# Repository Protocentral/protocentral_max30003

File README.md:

# ProtoCentral MAX30003 — Single‑lead ECG Breakout

Arduino library and examples for the MAX30003 single‑lead ECG analog front end.

## Highlights
- MAX30003 AFE: single‑lead ECG, ultra‑low power operation, integrated R‑R (RTOR) detection and QRS timing.
- Board: ProtoCentral breakout with level selection for 3.3V/5V systems, SPI interface, and INT pin for event/RTOR notifications.

## Quick features
- Single‑lead ECG measurement (24‑bit ADC samples)
- On‑chip R‑R (RTOR) detection and heart‑rate calculation
- Low power: suitable for battery powered wearables
- SPI interface; interrupt output for beat/flags

Wiring (Arduino defaults used in examples)

| MAX30003 signal | Arduino pin | Notes |
|-----------------|-------------|-------|
| MISO            | D12         | SPI MISO |
| MOSI            | D11         | SPI MOSI |
| SCLK            | D13         | SPI SCK  |
| CS              | D4          | Chip select (examples default) |
| INT1            | D2          | Interrupt / RTOR flag |
| VCC / 3V3       | 3.3V / 5V   | Power (match board jumper) |
| GND             | GND         | Ground |

## Quick start (example)

```cpp
#include <SPI.h>
#include "protocentral_max30003.h"

// Use chip select pin D4 (examples default)
MAX30003 max30003(4);

void setup() {
  Serial.begin(115200);
  SPI.begin();

  if (!max30003.readDeviceID()) {
    while (1) { delay(1000); }
  }

  max30003.begin();         // start sensor, default sampling
  max30003.setSamplingRate(MAX30003::SRATE_1000HZ); // optional: change sample rate
}

void loop() {
  int32_t ecg = 0;
  if (max30003.readEcgSample(ecg)) {   // returns true when a new sample is available
    Serial.println(ecg);               // 24‑bit sign‑extended ADC value
  }

  // RTOR / heart rate (library keeps latest values)
  max30003.updateHeartRate();
  Serial.print("HR:"); Serial.print(max30003.heartRate());
  Serial.print(" RR(ms):"); Serial.println(max30003.rrInterval());

  delay(8);
}
```

## Examples
- `examples/01-ecg-openview` — OpenView / UART packet streaming example
- `examples/02-ecg-plotter` — Arduino Serial Plotter output
- `examples/03-hr-rtor` — Heart‑rate and RTOR demonstration

## Build & upload using arduino-cli

```bash
arduino-cli compile --fqbn arduino:renesas_uno:minima --libraries /path/to/Arduino/libraries /path/to/protocentral_max30003/examples/02-ecg-plotter
arduino-cli upload -p /dev/ttyACM0 -b arduino:renesas_uno:minima -i /tmp/build/02-ecg-plotter.ino.bin
```

## Documentation & support
- Board and getting started: https://docs.protocentral.com/getting-started-with-max30003/
- Product page: https://www.protocentral.com/open-medical-devices/1149-protocentral-max30003-single-lead-ecg-breakout-board.html

## Licenses
- Hardware: CERN-OHL-P v2 (see `LICENSE.md`)
- Software: MIT (see `LICENSE.md`)

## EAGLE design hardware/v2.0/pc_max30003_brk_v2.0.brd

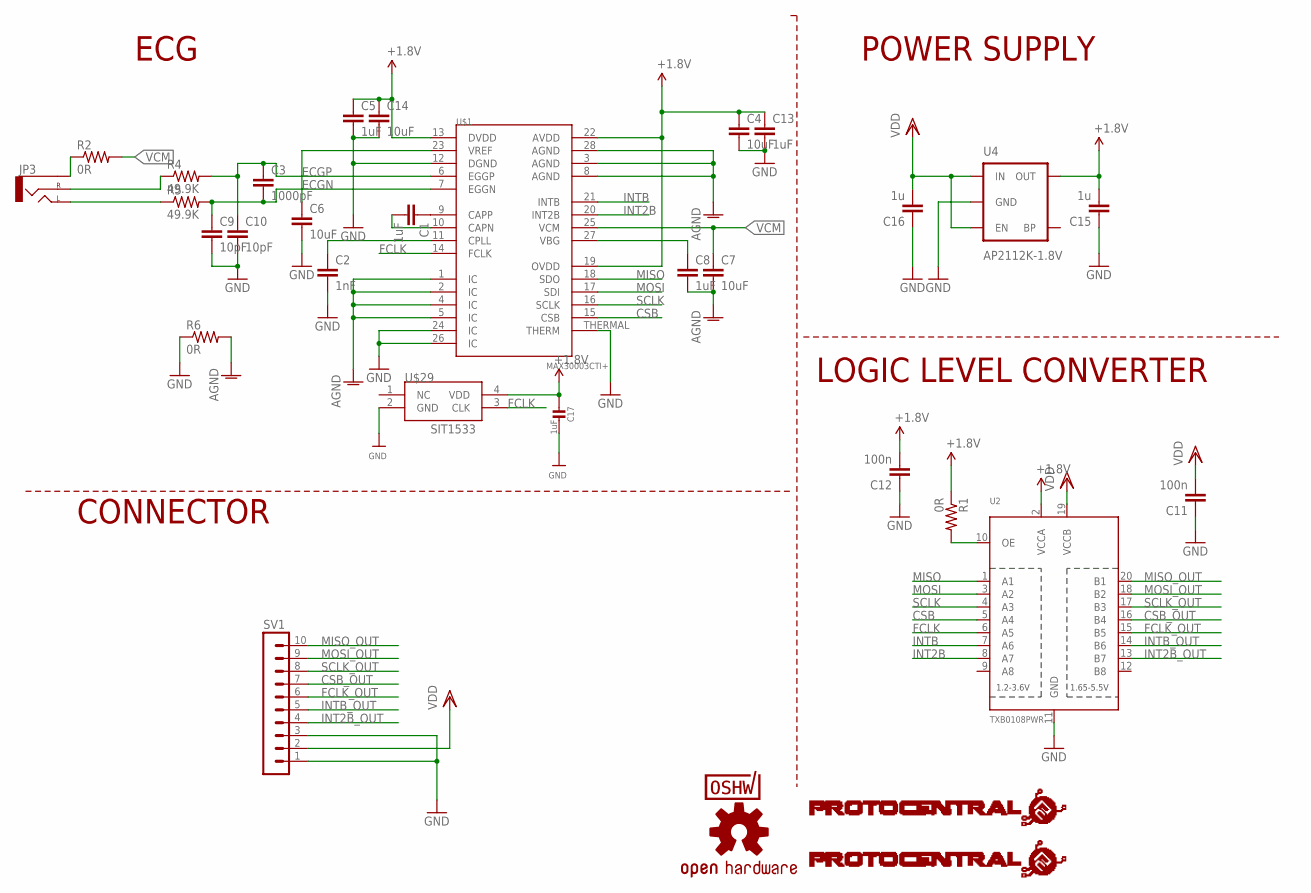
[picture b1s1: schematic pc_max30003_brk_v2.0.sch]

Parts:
C1, C5, C8, C13: 1uF; C0805
C2: 1nF; C0805
C3: 1000pF; C0402
C4, C6, C7, C14: 10uF; C0805
C9, C10: 10pF; C0402
C11, C12: 100n; C0402
C15, C16: 1u; C0805
C17: 1uF; _0402
JP3: AUDIO-JACKSMD2; AUDIO-JACK-3.5MM-SMD
R1, R2, R6: 0R; 0805
R4, R5: 49.9K; 0805
SV1: MA10-1
U2: TXB0108PWR; TSSOP20
U4: AP2112K-1.8V; SOT23-5
U$1: MAX30003CTI+; QFN-28
U$2: PROTY_LOGO_WITH_TEXT; PROTY_WITH_TEXT
U$3: PROTY-LOGO; LOGO-PROTY
U$6: OSHW-LOGOS; OSHW-LOGO-S
U$7: CERT-SMALL; CERT-SMALL-SILK
U$29: SIT1533

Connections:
+1.8V: C4.1, C5.1, C12.2, C13.1, C14.1, C15.2, C17.1, R1.1, U2.2 (VCCA), U4.5 (OUT), U$1.13 (DVDD), U$1.19 (OVDD), U$1.22 (AVDD), U$29.4 (VDD)
AGND: C7.2, C8.2, R6.2, U$1.1 (IC), U$1.2 (IC), U$1.3 (AGND), U$1.4 (IC), U$1.5 (IC), U$1.8 (AGND), U$1.28 (AGND)
CSB: U2.5 (A4), U$1.15 (CSB)
CSB_OUT: SV1.7, U2.16 (B4)
ECGN: C3.2, C9.1, R5.2, U$1.7 (EGGN)
ECGP: C3.1, C10.1, R4.2, U$1.6 (EGGP)
FCLK: U2.6 (A5), U$1.14 (FCLK), U$29.3 (CLK)
FCLK_OUT: SV1.6, U2.15 (B5)
GND: C2.2, C4.2, C5.2, C6.2, C9.2, C10.2, C11.1, C12.1, C13.2, C14.2, C15.1, C16.1, C17.2, R6.1, SV1.1, SV1.3, U2.11 (GND), U4.2 (GND), U$1.12 (DGND), U$1.24 (IC), U$1.26 (IC), U$1.THERMAL (THERM), U$29.2 (GND)
INT2B: U2.8 (A7), U$1.20 (INT2B)
INT2B_OUT: SV1.4, U2.13 (B7)
INTB: U2.7 (A6), U$1.21 (INTB)
INTB_OUT: SV1.5, U2.14 (B6)
MISO: U2.1 (A1), U$1.18 (SDO)
MISO_OUT: SV1.10, U2.20 (B1)
MOSI: U2.3 (A2), U$1.17 (SDI)
MOSI_OUT: SV1.9, U2.18 (B2)
unnamed: R1.2, U2.10 (OE)
unnamed: C6.1, U$1.23 (VREF)
unnamed: C1.1, U$1.9 (CAPP)
unnamed: JP3.SLEEVE, R2.1
unnamed: C1.2, U$1.10 (CAPN)
unnamed: C2.1, U$1.11 (CPLL)
unnamed: JP3.TIP (LEFT), R5.1
unnamed: JP3.RING (RIGHT), R4.1
unnamed: C8.1, U$1.27 (VBG)
SCLK: U2.4 (A3), U$1.16 (SCLK)
SCLK_OUT: SV1.8, U2.17 (B3)
VCM: C7.1, R2.2, U$1.25 (VCM)
VDD: C11.2, C16.2, SV1.2, U2.19 (VCCB), U4.1 (IN), U4.3 (EN)

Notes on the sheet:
ECG
POWER SUPPLY
LOGIC LEVEL CONVERTER
CONNECTOR

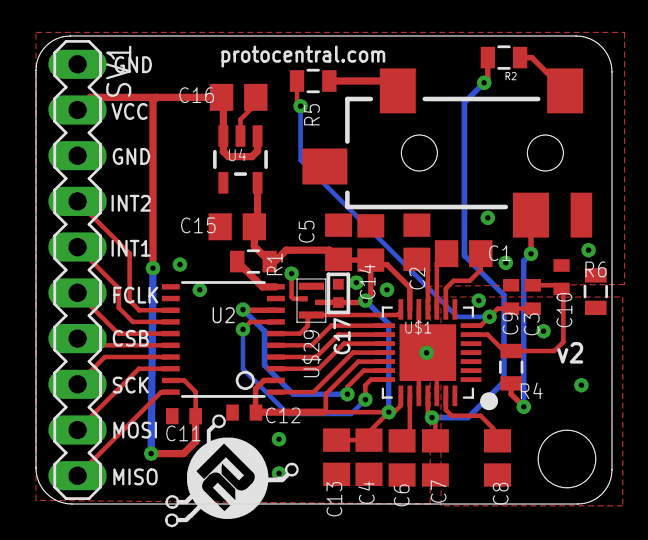
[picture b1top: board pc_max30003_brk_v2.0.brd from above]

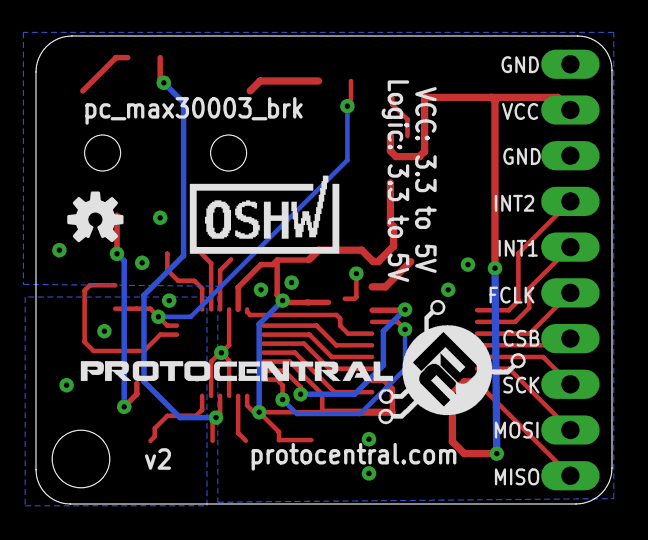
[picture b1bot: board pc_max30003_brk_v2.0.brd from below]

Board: 4 copper layers, 32.0 x 26.0 mm, 32 parts (3 on the bottom side), 30 nets.

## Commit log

2017-03-10 Reorganized structure, edited Readme.md
2017-03-10 updated the images
2017-03-10 upadted images
2017-03-17 updated heart rate
2017-03-18 Updated new code for processing GUI
2017-03-18 Updated License
2017-03-18 Updated license information
2017-08-02 updated design file
2017-08-02 upadted readme
2017-08-02 added v1.1 design files
2017-10-09 updated the ui
2018-04-19 Updated readme and images
2018-07-13 added basic code
2018-09-14 Reduced the sampling rate to 128 and commented fclock generation code
2018-11-15 Added later hardware revisions
2020-12-31 Rearranged docs inside repo
2020-12-31 Added OpenView links
2021-01-01 Reorganized Arduino library
2021-03-26 Update License Information
2022-04-24 Fixed example file error
2022-11-17 Adding CI build action
2022-11-18 Add Arduino AVR to checked platforms.
2022-11-18 Pin workflow version to v1.
2022-11-18 Add CI compile badge.
2022-11-25 Migrated to SPISettings in library
2022-11-25 Fixed SPI mode
2022-11-25 Fix OpenView example
2025-09-12 Initial Migration to more modern API
2025-09-12 Bump version
2025-09-12 Add extra API functions

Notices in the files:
parts and their libraries:
SparkFun-PowerIC: Licensing: Creative Commons ShareAlike 4.0 International - https://creativecommons.org/licenses/by-sa/4.0
microbuilder: This work is placed in the public domain, and may be freely used for commercial and non-commercial work with the following conditions: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
